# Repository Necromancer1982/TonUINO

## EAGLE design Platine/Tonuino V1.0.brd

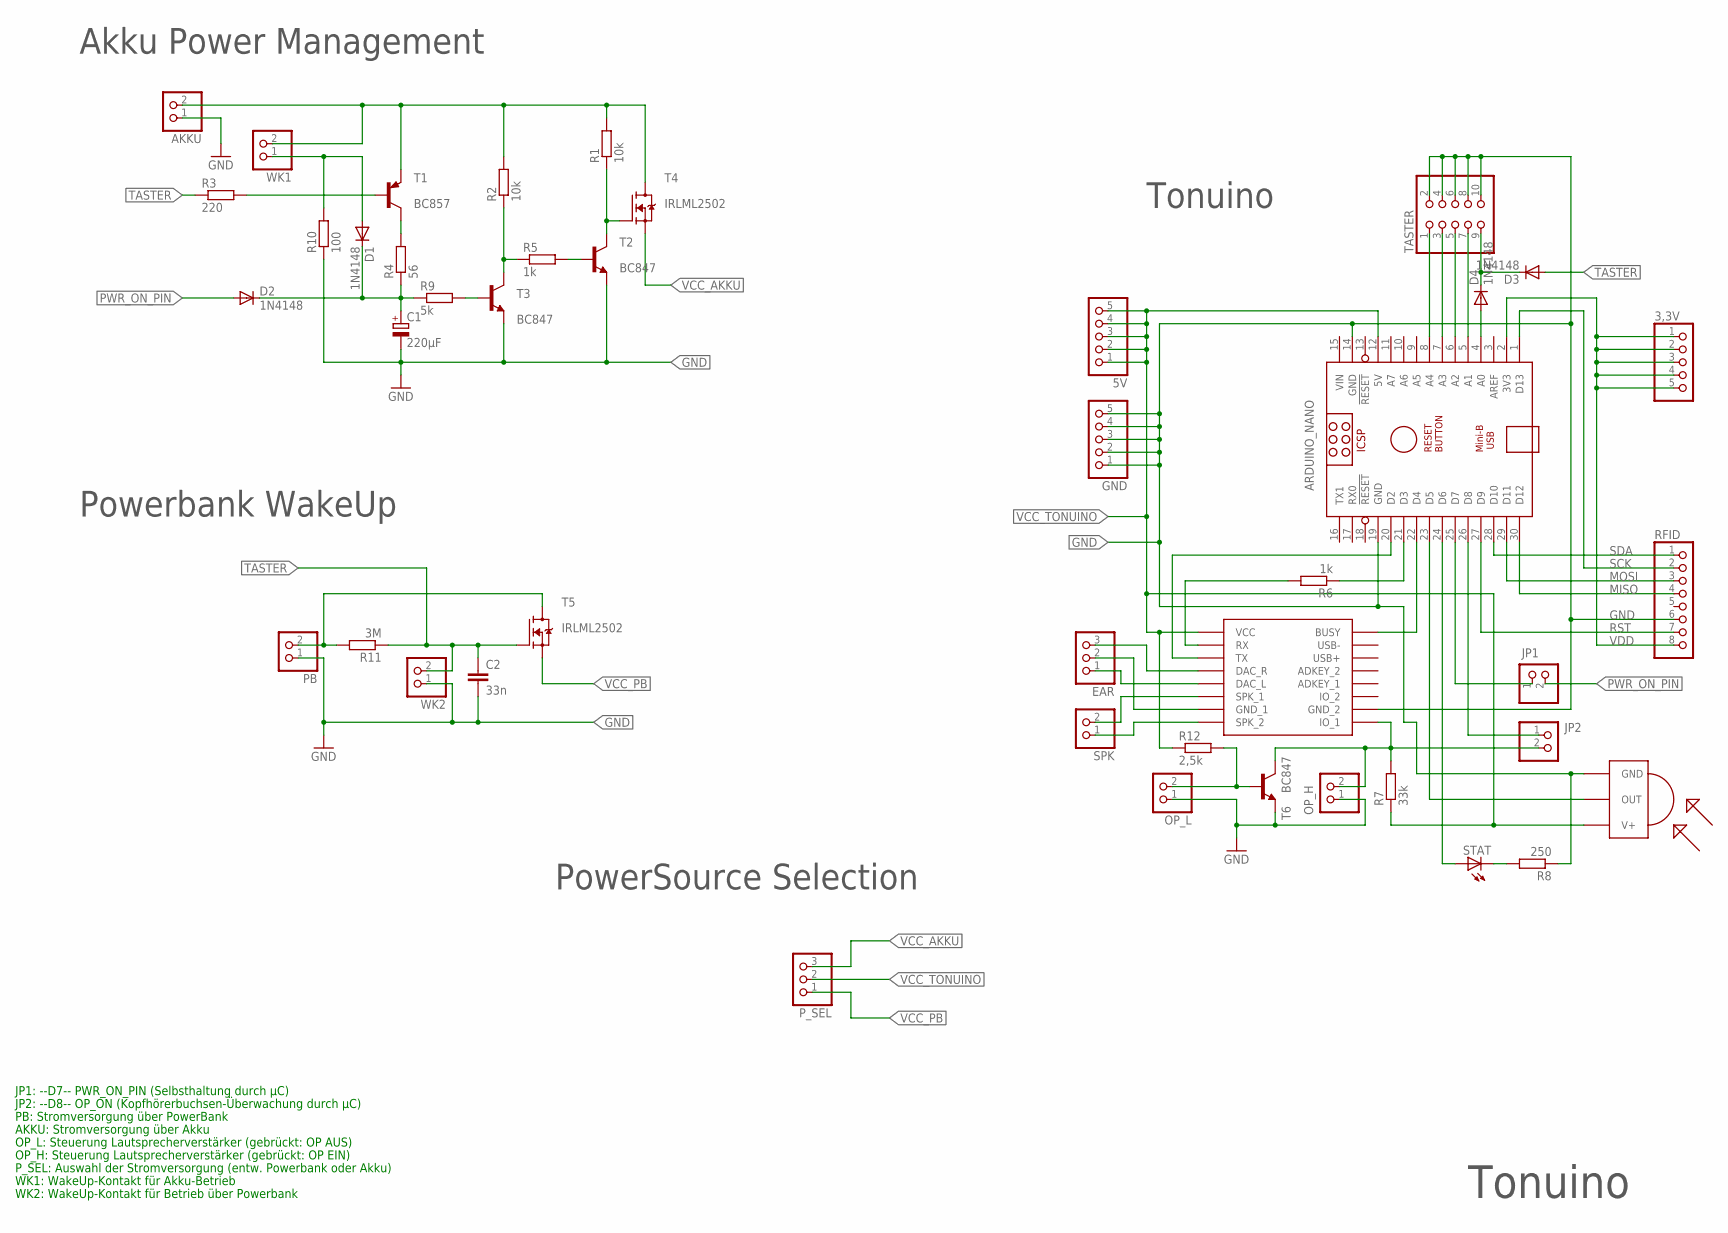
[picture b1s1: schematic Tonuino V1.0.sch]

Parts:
3,3V, 5V: PINHD-1X5; 1X05
AKKU: PINHD-1X2; 1X02
ARDUINO_NANO: ARDUINO_NANO
C1: 220µF; E5-13
C2: 33n; C0805
D1, D2, D3, D4: 1N4148; SOD323-W
EAR: PINHD-1X3; 1X03
GND: PINHD-1X5; 1X05
JP1, JP2: PINHD-1X2; 1X02
OP_H: PINHD-1X2; 1X02
OP_L: PINHD-1X2; 1X02
PB: PINHD-1X2; 1X02
P_SEL: PINHD-1X3; 1X03
R1, R2: 10k; R1206
R3: 220; R1206
R4: 56; R1206
R5, R6: 1k; R1206
R7: 33k; R1206
R8: 250; R1206
R9: 5k; R1206
R10: 100; R1206
R11: 3M; R1206
R12: 2,5k; R1206
RFID: PINHD-1X8; 1X08
SPK: PINHD-1X2; 1X02
STAT: LED5MM
T1: BC857; SOT23-BEC
T2, T3, T6: BC847; SOT23
T4, T5: IRLML2502; SOT23
TASTER: PINHD-2X5; 2X05
TSOP1: TSOP1730; TSOP17XX
U$2: DFPLAYER
WK1, WK2: PINHD-1X2; 1X02

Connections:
GND: AKKU.1, ARDUINO_NANO.14 (GND), ARDUINO_NANO.19 (GND), C1.-, C2.2, GND.1, GND.2, GND.3, GND.4, GND.5, OP_H.1, OP_L.1, PB.1, R8.1, R10.1, RFID.6, T2.2 (E), T3.2 (E), T6.2 (E), TASTER.2, TASTER.4, TASTER.6, TASTER.8, TASTER.10, TSOP1.GND, U$2.GND_2, WK2.1
MISO: ARDUINO_NANO.30 (D12), RFID.4
MOSI: ARDUINO_NANO.29 (D11), RFID.3
unnamed: SPK.1, U$2.SPK2 (SPK_2)
unnamed: SPK.2, U$2.SPK1 (SPK_1)
unnamed: EAR.2, U$2.GND_1
unnamed: EAR.1, U$2.DAC_L
unnamed: EAR.3, U$2.DAC_R
unnamed: R6.2, U$2.RX
unnamed: ARDUINO_NANO.21 (D3), R6.1
unnamed: ARDUINO_NANO.20 (D2), U$2.TX
unnamed: ARDUINO_NANO.22 (D4), U$2.BUSY
unnamed: JP2.2, OP_H.2, R7.2, T6.3 (C), U$2.IO1 (IO_1)
unnamed: R3.2, T1.B
unnamed: D3.C, D4.C, TASTER.9
unnamed: ARDUINO_NANO.5 (A1), TASTER.7
unnamed: ARDUINO_NANO.6 (A2), TASTER.5
unnamed: ARDUINO_NANO.7 (A3), TASTER.3
unnamed: R8.2, STAT.K (C)
unnamed: ARDUINO_NANO.26 (D8), JP2.1
unnamed: R4.2, T1.C
unnamed: ARDUINO_NANO.8 (A4), TASTER.1
unnamed: PB.2, R11.2, T5.3 (D)
unnamed: ARDUINO_NANO.23 (D5), TSOP1.OUT
unnamed: ARDUINO_NANO.24 (D6), STAT.A
unnamed: OP_L.2, R12.2, T6.1 (B)
unnamed: C1.+, D1.C, D2.C, R4.1, R9.1
unnamed: D1.A, R10.2, WK1.1
unnamed: ARDUINO_NANO.4 (A0), D4.A
unnamed: R9.2, T3.1 (B)
unnamed: R2.1, R5.1, T3.3 (C)
unnamed: R5.2, T2.1 (B)
unnamed: R1.1, T2.3 (C), T4.1 (G)
PWR_ON_PIN: D2.A, JP1.2
PWR_ON_PIN_JPR: ARDUINO_NANO.25 (D7), JP1.1
RST: ARDUINO_NANO.27 (D9), RFID.7
SCK: ARDUINO_NANO.1 (D13), RFID.2
SDA: ARDUINO_NANO.28 (D10), RFID.1
TASTER: C2.1, D3.A, R3.1, R11.1, T5.1 (G), WK2.2
VCC: AKKU.2, R1.2, R2.2, T1.E, T4.3 (D), WK1.2
VCC_AKKU: P_SEL.3, T4.2 (S)
VCC_PB: P_SEL.1, T5.2 (S)
VCC_TONUINO: 5V.1, 5V.2, 5V.3, 5V.4, 5V.5, ARDUINO_NANO.12 (5V), P_SEL.2, R7.1, R12.1, TSOP1.V+, U$2.VCC
VDD: 3,3V.1, 3,3V.2, 3,3V.3, 3,3V.4, 3,3V.5, ARDUINO_NANO.2 (3V3), RFID.8
VIN: ARDUINO_NANO.15 (VIN)

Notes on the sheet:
Akku Power Management
Tonuino
JP1: --D7-- PWR_ON_PIN (Selbsthaltung durch µC)
JP2: --D8-- OP_ON (Kopfhörerbuchsen-Überwachung durch µC)
AKKU: Stromversorgung über Akku
OP_H: Steuerung Lautsprecherverstärker (gebrückt: OP EIN)
Powerbank WakeUp
PowerSource Selection
P_SEL: Auswahl der Stromversorgung (entw. Powerbank oder Akku)
WK1: WakeUp-Kontakt für Akku-Betrieb
WK2: WakeUp-Kontakt für Betrieb über Powerbank
PB: Stromversorgung über PowerBank
OP_L: Steuerung Lautsprecherverstärker (gebrückt: OP AUS)

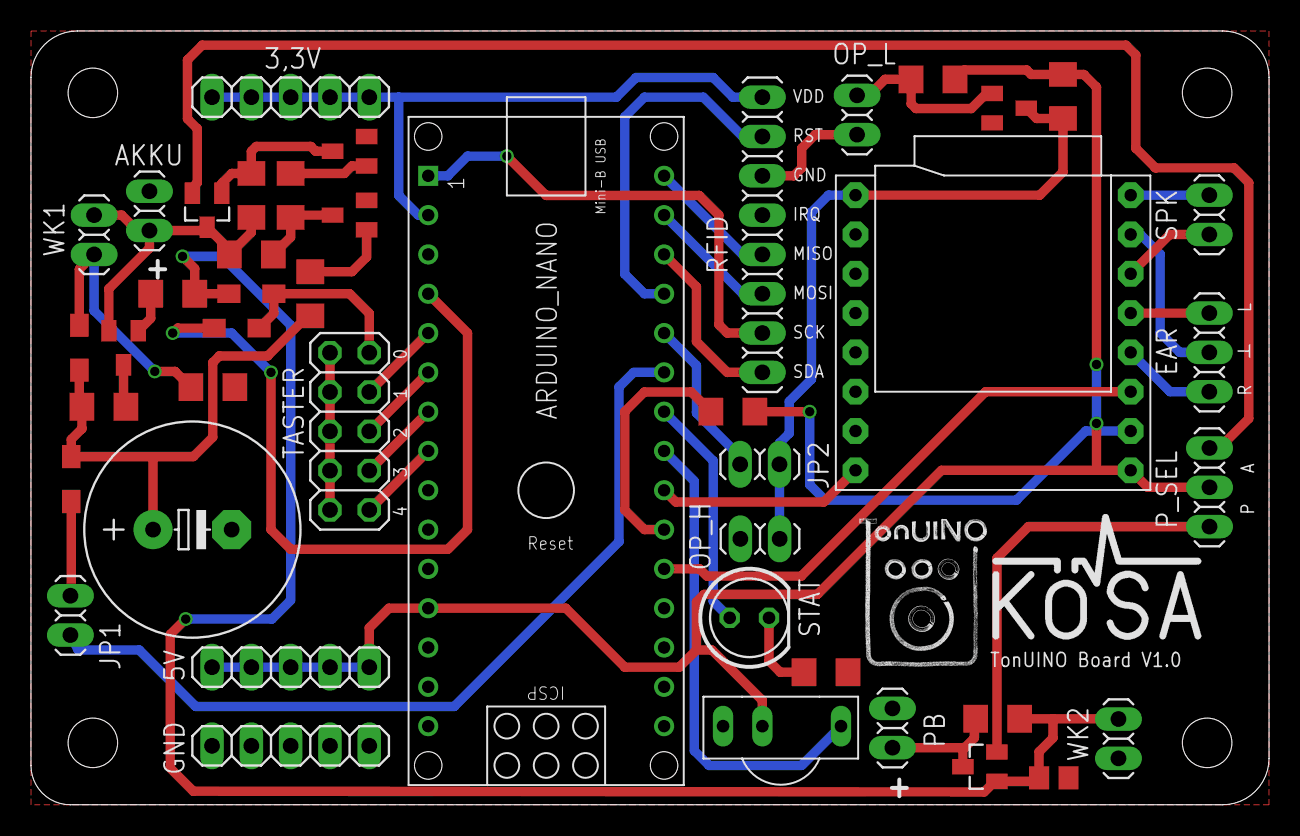
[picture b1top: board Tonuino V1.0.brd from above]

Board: 2 copper layers, 80.0 x 50.0 mm, 44 parts (0 on the bottom side), 44 nets.

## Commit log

2019-05-10 Erweitere Sound-Dateien / Extended Sound-Files
    ZIP-Archiv entpacken und die beiden Ordenr "mp3" und "advert" auf der SD-Karte ablegen /
    Extract ZIP-File and put both folders "mp3" and "advert" to SD-Card
